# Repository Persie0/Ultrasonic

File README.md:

# Ultrasonic audio bench prototypes

Two independent design families, five editable KiCad projects. **These are electrical prototypes, not finished or exposure-certified speakers.** Start with a dummy capacitor and the arm link open.

| Design | Hardware | Build and test |
|---|---|---|
| [ESP32 original](designs/esp32-digital/) | External ESP32 DevKit, 5 V driver | [Build](designs/esp32-digital/BUILD.md) · [Test](designs/esp32-digital/TEST.md) |
| [ESP32 passive](designs/esp32-digital/minimum-cost/) | Four resistors; lowest additional parts cost | [Guide](designs/esp32-digital/minimum-cost/README.md) |
| [ESP32 integrated](designs/esp32-digital/integrated/) | USB power/programming, onboard ESP32, ten DNP positions | [Illustrated guide](designs/esp32-digital/integrated/BUILD_TEST.md) |
| [Analog DDS](designs/analog-dds/) | External DDS, Nano and analog line source | [Build](designs/analog-dds/BUILD.md) · [Test](designs/analog-dds/TEST.md) |
| [GreatScott reference PWM](designs/analog-dds/reference-pwm/) | Reference-derived logic controller, no power stage | [Guide](designs/analog-dds/reference-pwm/BUILD_TEST.md) |

The ten optional positions share one current-limited output, not ten independently powered channels. The passive load sweep predicts sharply reduced voltage as capacitance increases; a working ten-speaker system is not demonstrated.

## Verification

- [Original designs: CI 45840044890](https://github.com/Persie0/Playground/actions/runs/45840044890): three clean KiCad projects, ESP32 and three Arduino builds, 243 RC cases.
- [New designs: CI 45846640684](https://github.com/Persie0/Playground/actions/runs/45846640684): two clean KiCad projects, 6,480 comparison cases, 4,860 ten-load cases and 648 power sensitivity cases (106 power cases outside assumed limits).
- [Review and release gates](VALIDATION.md): 263 unique pin/net matches across five designs, all verified; physical/RF/USB/power and acoustic gates remain.

Original GreatScott Arduino sketch is committed unchanged; the supplied PDF and Gerber ZIP are verified but not yet uploaded. See [source inventory](designs/analog-dds/SOURCE_FILES.md). The owner confirms permission to reshare the attachments.

No fabrication release. No acoustic output guarantee. Do not fit an acoustic load until the separate qualified exposure and hardware review is complete.

For the integrated board, see the [power-only bring-up](designs/esp32-digital/integrated/POWER_TEST.md) and [USB power review](designs/esp32-digital/integrated/POWER_REVIEW.md) before any audio tests.

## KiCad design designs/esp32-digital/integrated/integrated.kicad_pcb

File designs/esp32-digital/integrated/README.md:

# Integrated USB-powered ESP32 bench board

One PCB, no external development board, DDS, audio receiver or programmer. Original ESP32-WROOM-32E-N4 module soldered directly to PCB, AP7361C-33E-13 SOT223 regulator, CH340C USB-UART with built-in clock, USB-B power/data connector, boot/reset switches, current-limited passive output and ten optional on-board 40 kHz load footprints (all DNP). Default assembly is the 2.7 nF electrical dummy load with arm solder bridge open. Ten positions share the same current-limited differential circuit; they are not independent amplifier channels. TP1 is an unpopulated probe location. USB only for power and firmware flashing; Bluetooth Classic A2DP after flashing. No change to existing firmware or drive limits. Actual audible output and acoustic safety not established; do not fit transmitter until qualified testing. No external power amplifier, oscillator, or adjustment needed.

Board 68 × 87 mm, two layers, 31 footprints, 123 pads, 312 segments, 38 vias. Source-derived pad geometries from KiCad ESP32-WROOM-32, SOT-223, SOIC-16, TE USB-B vertical, 0805/1206 and TL3342; local simplified footprints; verify package dimensions, connector variant, exposed-pad stencil, thermal copper, antenna clearance and solder mask against datasheets. The antenna overhangs top edge; keep metal/enclosure away. Native KiCad 9 ERC/DRC passed with zero violations in [run 45846640684](https://github.com/Persie0/Playground/actions/runs/45846640684); 118 unique schematic pin IDs matched PCB nets. RF/USB/thermal/mechanical review remains pending. No fabrication release.

## Power and programming

USB power is a regulated 5 V input. The ESP32 supply design needs burst-current capability; this board is not verified to meet USB enumeration current limits or regulator thermal limits. Do not assume an arbitrary computer port is suitable. A powered data host does not by itself establish USB compliance. AP7361C fixed SOT223 pin 1 input, pin 2 ground, pin 3 output, tab ground; do not substitute the reversed SOT223R pinout. CH340C is powered at 3.3 V (V3 tied to VCC), RX/TX crossed; R232 has an internal pull-down in the documented device. Verify the exact device lot/datasheet. The regulator is nominally rated 1 A, but this PCB is not thermally qualified at 500 mA or 1 A. Hold BOOT, pulse RESET, release BOOT, then flash using esptool/ESP-IDF with manual reset (no automatic DTR/RTS circuit). For programming use a suitable powered USB host; unplug after flashing, use USB supply and pair Bluetooth. Keep JP1 open. Fit C7 dummy only for electrical testing. Never connect external voltage or grounded test clip to either differential terminal.

## References

- https://documentation.espressif.com/esp32-wroom-32e_esp32-wroom-32ue_datasheet_en.html
- https://docs.espressif.com/projects/esp-hardware-design-guidelines/en/latest/esp32/schematic-checklist.html
- https://www.diodes.com/datasheet/download/AP7361C.pdf
- https://www.wch-ic.com/products/CH340.html
- https://www.murata.com/-/media/webrenewal/products/sensor/ultrasonic/open/datasheet_maopn.ashx

No full-power acoustic mode. The ten positions remain unpopulated by default. See [ten-load model](ten_load_simulation.md). See [build/test](BUILD_TEST.md) and [power model](power_simulation.md).

## Review status

See [overall release gates](../../../VALIDATION.md). A native DRC pass does not establish a verified RF ground plane, USB impedance/ESD compliance, regulator transient response or acoustic operation.

## Power-only diagnostic and revised USB review

Start with [POWER_TEST.md](POWER_TEST.md), not the audio firmware. [POWER_REVIEW.md](POWER_REVIEW.md) documents 756 additional screening cases, verified datasheet conditions and USB limitations. No PCB or output change in this review; no hardware release.

## Local ground-copper candidate

See [layout audit and candidate generation](POWER_COPPER.md). The existing validated PCB is retained; the proposed local ground zones are generated separately and require native fill and DRC. They are not a fabrication release or a measured thermal improvement.

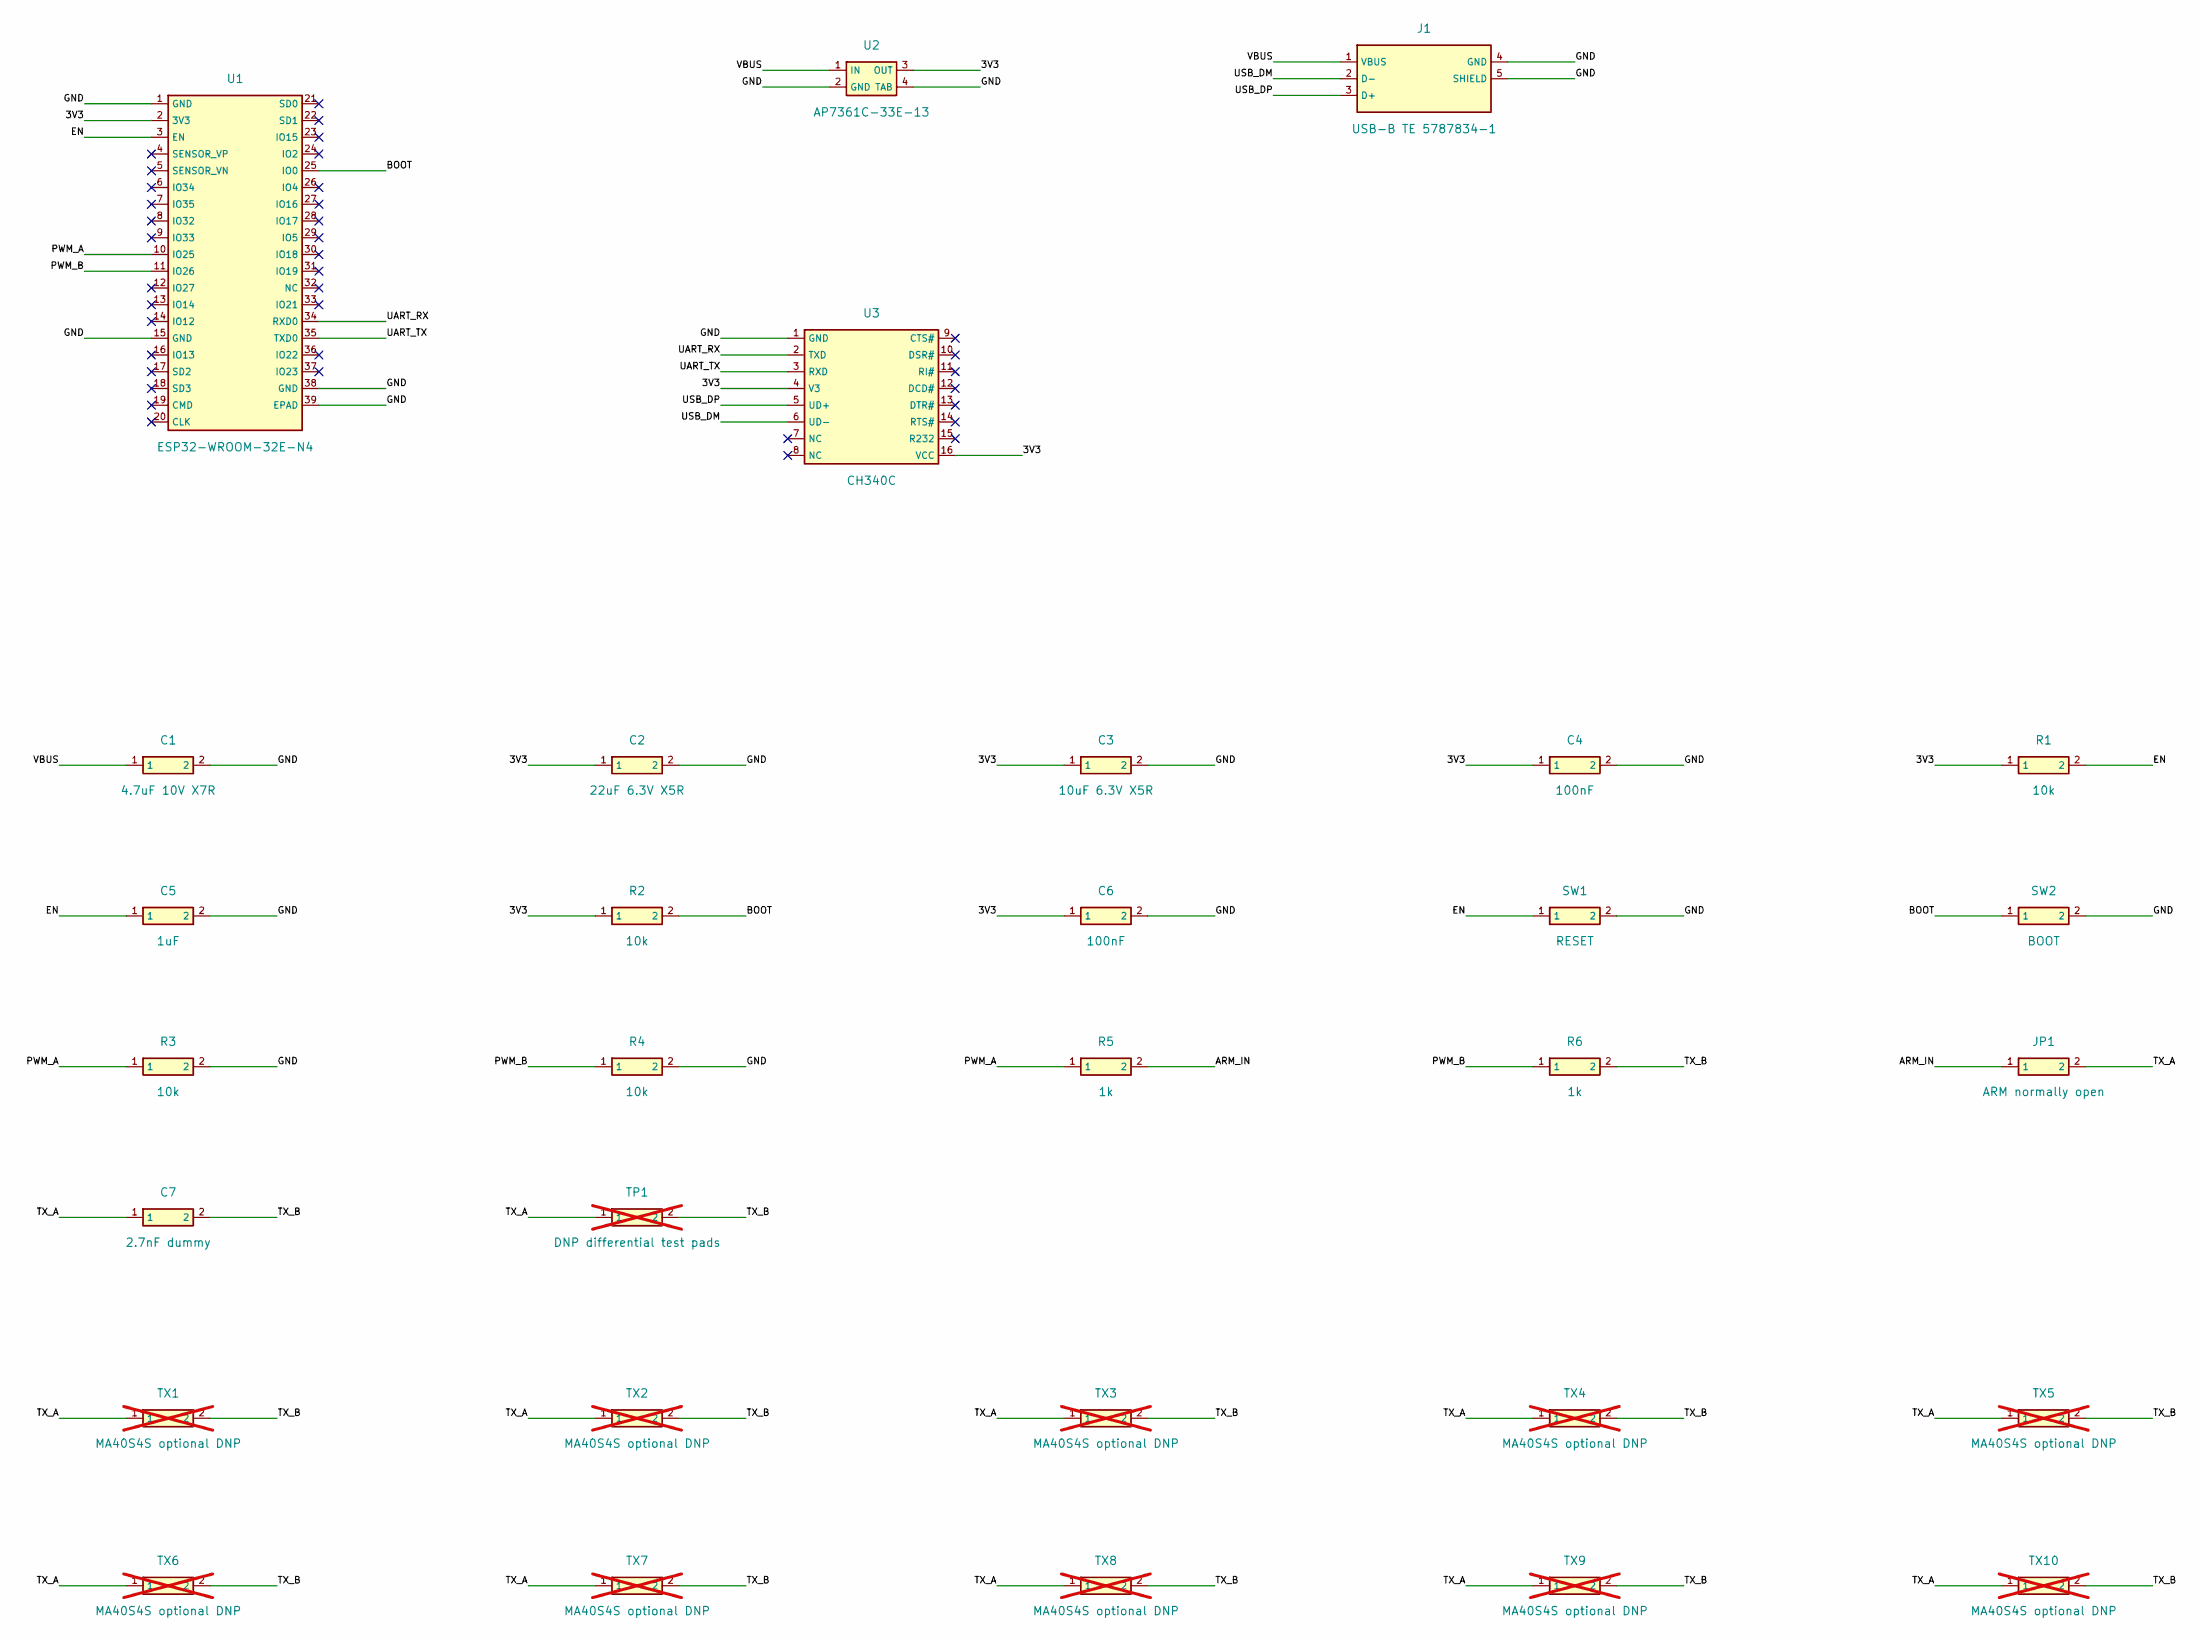
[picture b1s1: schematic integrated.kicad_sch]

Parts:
C1: 4.7uF 10V X7R; C1206
C2: 22uF 6.3V X5R; C1206
C3: 10uF 6.3V X5R; C1206
C4, C6: 100nF; C0805
C5: 1uF; C0805
C7: 2.7nF dummy; C0805
J1: USB-B TE 5787834-1; USB_B_VERTICAL
JP1: ARM normally open; SOLDERJUMPER
R1, R2, R3, R4: 10k; R0805
R5, R6: 1k; R0805
SW1: RESET; TACT_TL3342
SW2: BOOT; TACT_TL3342
TP1: DNP differential test pads; MA40S4S; not fitted
TX1, TX2, TX3, TX4, TX5, TX6, TX7, TX8, TX9, TX10: MA40S4S optional DNP; MA40S4S; not fitted
U1: ESP32-WROOM-32E-N4; ESP32_WROOM_32E
U2: AP7361C-33E-13; SOT223
U3: CH340C; SOIC16

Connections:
3V3: C2.1, C3.1, C4.1, C6.1, R1.1, R2.1, U1.2 (3V3), U2.3 (OUT), U3.4 (V3), U3.16 (VCC)
ARM_IN: JP1.1, R5.2
BOOT: R2.2, SW2.1, U1.25 (IO0)
EN: C5.1, R1.2, SW1.1, U1.3 (EN)
GND: C1.2, C2.2, C3.2, C4.2, C5.2, C6.2, J1.4 (GND), J1.5 (SHIELD), R3.2, R4.2, SW1.2, SW2.2, U1.1 (GND), U1.15 (GND), U1.38 (GND), U1.39 (EPAD), U2.2 (GND), U2.4 (TAB), U3.1 (GND)
PWM_A: R3.1, R5.1, U1.10 (IO25)
PWM_B: R4.1, R6.1, U1.11 (IO26)
TX_A: C7.1, JP1.2, TP1.1, TX1.1, TX2.1, TX3.1, TX4.1, TX5.1, TX6.1, TX7.1, TX8.1, TX9.1, TX10.1
TX_B: C7.2, R6.2, TP1.2, TX1.2, TX2.2, TX3.2, TX4.2, TX5.2, TX6.2, TX7.2, TX8.2, TX9.2, TX10.2
UART_RX: U1.34 (RXD0), U3.2 (TXD)
UART_TX: U1.35 (TXD0), U3.3 (RXD)
USB_DM: J1.2 (D-), U3.6 (UD-)
USB_DP: J1.3 (D+), U3.5 (UD+)
VBUS: C1.1, J1.1 (VBUS), U2.1 (IN)

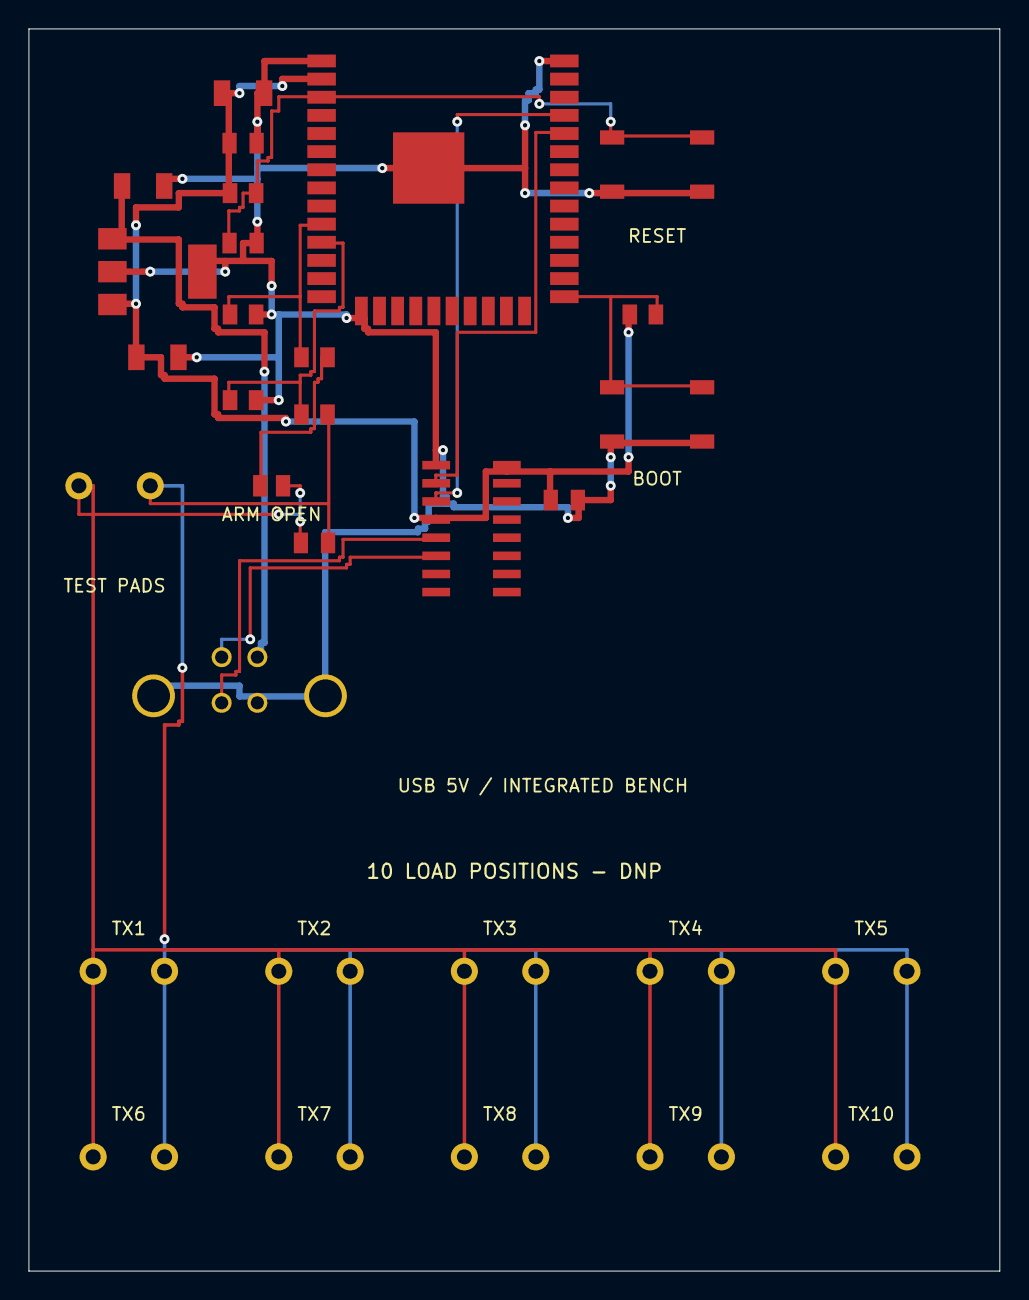
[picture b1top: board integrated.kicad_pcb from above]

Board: 2 copper layers, 68.0 x 87.0 mm, 31 parts (0 on the bottom side), 14 nets.

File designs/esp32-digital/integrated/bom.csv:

Reference,Quantity,Value,Footprint,Assembly
U1,1,ESP32-WROOM-32E-N4,ESP32_WROOM_32E,Fit
U2,1,AP7361C-33E-13,SOT223,Fit
U3,1,CH340C,SOIC16,Fit
J1,1,USB-B TE 5787834-1,USB_B_VERTICAL,Fit
C1,1,4.7uF 10V X7R,C1206,Fit
C2,1,22uF 6.3V X5R,C1206,Fit
C3,1,10uF 6.3V X5R,C1206,Fit
C4,1,100nF,C0805,Fit
R1,1,10k,R0805,Fit
C5,1,1uF,C0805,Fit
R2,1,10k,R0805,Fit
C6,1,100nF,C0805,Fit
SW1,1,RESET,TACT_TL3342,Fit
SW2,1,BOOT,TACT_TL3342,Fit
R3,1,10k,R0805,Fit
R4,1,10k,R0805,Fit
R5,1,1k,R0805,Fit
R6,1,1k,R0805,Fit
JP1,1,ARM normally open,SOLDERJUMPER,Fit
C7,1,2.7nF dummy,C0805,Fit
TP1,1,DNP differential test pads,MA40S4S,DNP
TX1,1,MA40S4S optional DNP,MA40S4S,DNP
TX2,1,MA40S4S optional DNP,MA40S4S,DNP
TX3,1,MA40S4S optional DNP,MA40S4S,DNP
TX4,1,MA40S4S optional DNP,MA40S4S,DNP
TX5,1,MA40S4S optional DNP,MA40S4S,DNP
TX6,1,MA40S4S optional DNP,MA40S4S,DNP
TX7,1,MA40S4S optional DNP,MA40S4S,DNP
TX8,1,MA40S4S optional DNP,MA40S4S,DNP
TX9,1,MA40S4S optional DNP,MA40S4S,DNP
TX10,1,MA40S4S optional DNP,MA40S4S,DNP

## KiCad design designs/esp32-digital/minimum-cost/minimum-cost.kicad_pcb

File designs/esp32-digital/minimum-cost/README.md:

# Minimum-cost passive-only ESP32 bench interface

Independent lower-output variant of the validated TC4427A board. Same firmware and original ESP32 DevKit; no extra IC or 5 V power input on this PCB. Four resistors, three inexpensive headers and one removable shunt. 31 x 24 mm, two layers, 15 pads, 18 tracks, no vias. Static clearance minimum 0.746 mm and all six nets connected; native KiCad ERC/DRC passed with zero violations in [run 45846640684](https://github.com/Persie0/Playground/actions/runs/45846640684). All 15 unique pin IDs matched PCB nets. Estimated passive BOM EUR 0.15–0.70 before shipping, PCB and ESP32; prices are planning assumptions rather than quotes. The cheapest electrical prototype uses existing breadboard/jumper wires instead of ordering a PCB. This board is not a performance-equivalent alternative to the TC4427A; lower voltage and higher series resistance substantially reduce output. It is intended for isolated capacitive dummy loads only until physical validation and an appropriate acoustic exposure review. Never connect an array, amplifier, external supply or grounded load to the output.

## Build and test

Inspect the KiCad project, verify ERC/DRC and physical component fit before ordering. Solder four resistors and headers; leave J2 open. J1 pin 1 common ground, pin 2 GPIO25, pin 3 GPIO26. No 5 V or 3.3 V supply pin. J3 is differential, neither pin is ground. Flash the unchanged [ESP32 firmware](../firmware/) with the board disconnected. Power only the DevKit normally; check the pins at idle and during streaming with an oscilloscope referenced only to DevKit ground. Power off, fit a nonpolar 2.2–2.7 nF dummy capacitor at J3, and close J2 only during supervised electrical tests. Verify boot/pause/disconnect muting, check each GPIO output and differential voltage with two grounded channels and math subtraction, record current and temperature, then power off and remove the jumper. No acoustic validation or manufacture approval. See [simulation](../simulation/minimum_cost.md).

Physical and acoustic validation remain pending. See [review](../../../VALIDATION.md).

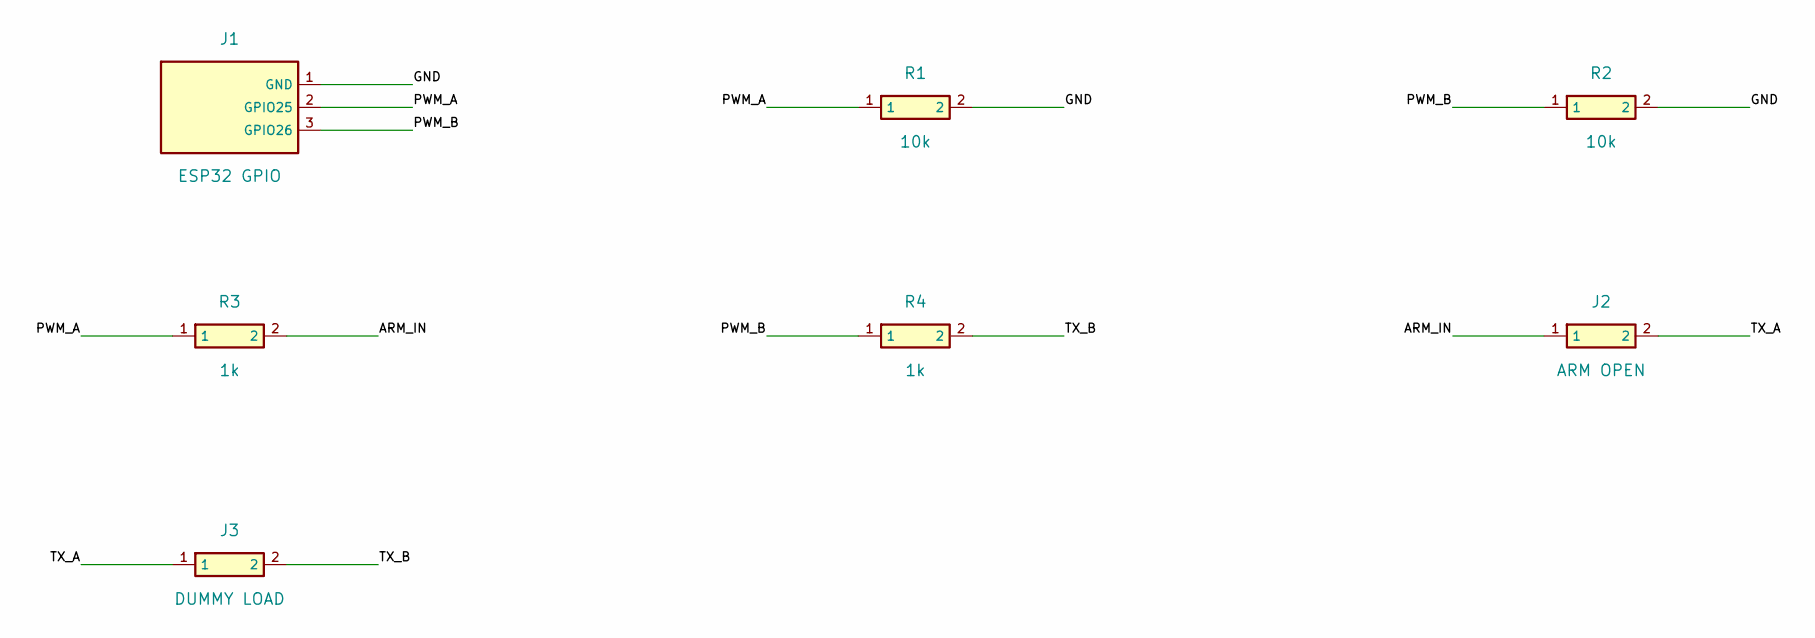
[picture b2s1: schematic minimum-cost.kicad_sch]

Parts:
J1: ESP32 GPIO; Header3
J2: ARM OPEN; Header2H
J3: DUMMY LOAD; Header2V
R1, R2: 10k; Axial
R3, R4: 1k; Axial

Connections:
ARM_IN: J2.1, R3.2
GND: J1.1 (GND), R1.2, R2.2
PWM_A: J1.2 (GPIO25), R1.1, R3.1
PWM_B: J1.3 (GPIO26), R2.1, R4.1
TX_A: J2.2, J3.1
TX_B: J3.2, R4.2

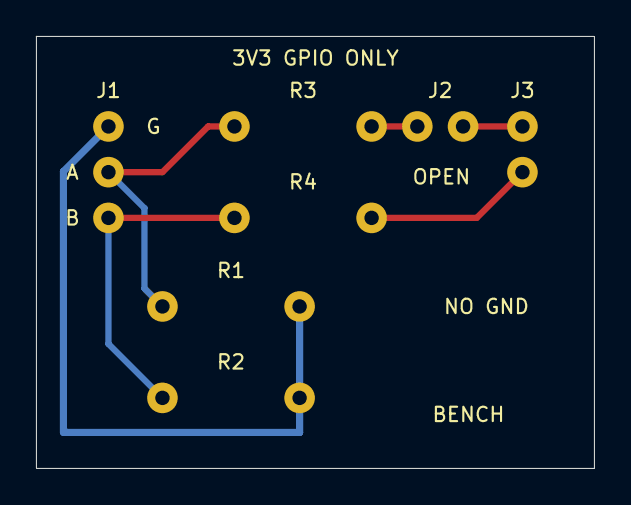
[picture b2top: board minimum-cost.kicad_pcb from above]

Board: 2 copper layers, 31.0 x 24.0 mm, 7 parts (0 on the bottom side), 6 nets.

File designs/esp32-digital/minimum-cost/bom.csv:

Reference,Quantity,Value,Notes
R1 R2,2,10k,axial 1/4W 7.62mm
R3 R4,2,1k,axial 1/4W 7.62mm
J1,1,1x3 2.54mm header,GPIO and common GND only
J2,1,1x2 2.54mm header and shunt,open by default
J3,1,1x2 2.54mm header,differential dummy load; neither pin ground
MOD1,1,ESP32-WROOM-32 DevKit,original Bluetooth Classic capable ESP32

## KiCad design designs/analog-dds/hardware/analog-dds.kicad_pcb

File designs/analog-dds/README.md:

# Analog DDS prototype (GreatScott-inspired)

Independent low-voltage analog comparator experiment, based on the general architecture discussed in [GreatScott's directional speaker video](https://www.youtube.com/watch?v=B8ss4KqcuXU) and [project post](https://www.patreon.com/GreatScott/posts/directional-119558088). The original schematic PDF, Arduino sketch and transmitter Gerbers were subsequently supplied and inspected. See [source inventory](SOURCE_FILES.md). The fixed-bias board below remains an independent alternative, not the creator's circuit. A separate [reference-derived PWM controller PCB](reference-pwm/) preserves the original analog topology and adjustments.

The supplied schematic uses Arduino Nano, AD9833, MCP602, LM393 and potentiometers, and ends at PWMOUT. The H-bridge power stage is not included in the supplied schematic. This independent version instead uses an external Nano + AD9833 module, external Bluetooth line-out module, fixed passive bias/attenuation, LM393 comparator and TC4427A single-ended 5 V output. The second comparator and driver channels are unused and defined. No trimmers, no high-voltage power stage, no array. An output coupling capacitor blocks steady DC; J4 is a normally-open arm jumper. The fixed bias is only appropriate for a verified raw low-voltage triangle output; not all DDS modules expose the same waveform. Audio compatibility and audible output are not demonstrated.

- [KiCad PCB and schematic](hardware/)
- [Build tutorial](BUILD.md)
- [Test tutorial](TEST.md)
- [BOM](hardware/bom.csv)
- [Nano DDS sketch](firmware/dds_setup/dds_setup.ino)

Experimental single-transmitter/dummy-load design only. Native ERC and DRC passed with zero violations (see [validation](VALIDATION.md)); physical and acoustic validation are outstanding; do not fabricate or use until the release gates are reviewed.

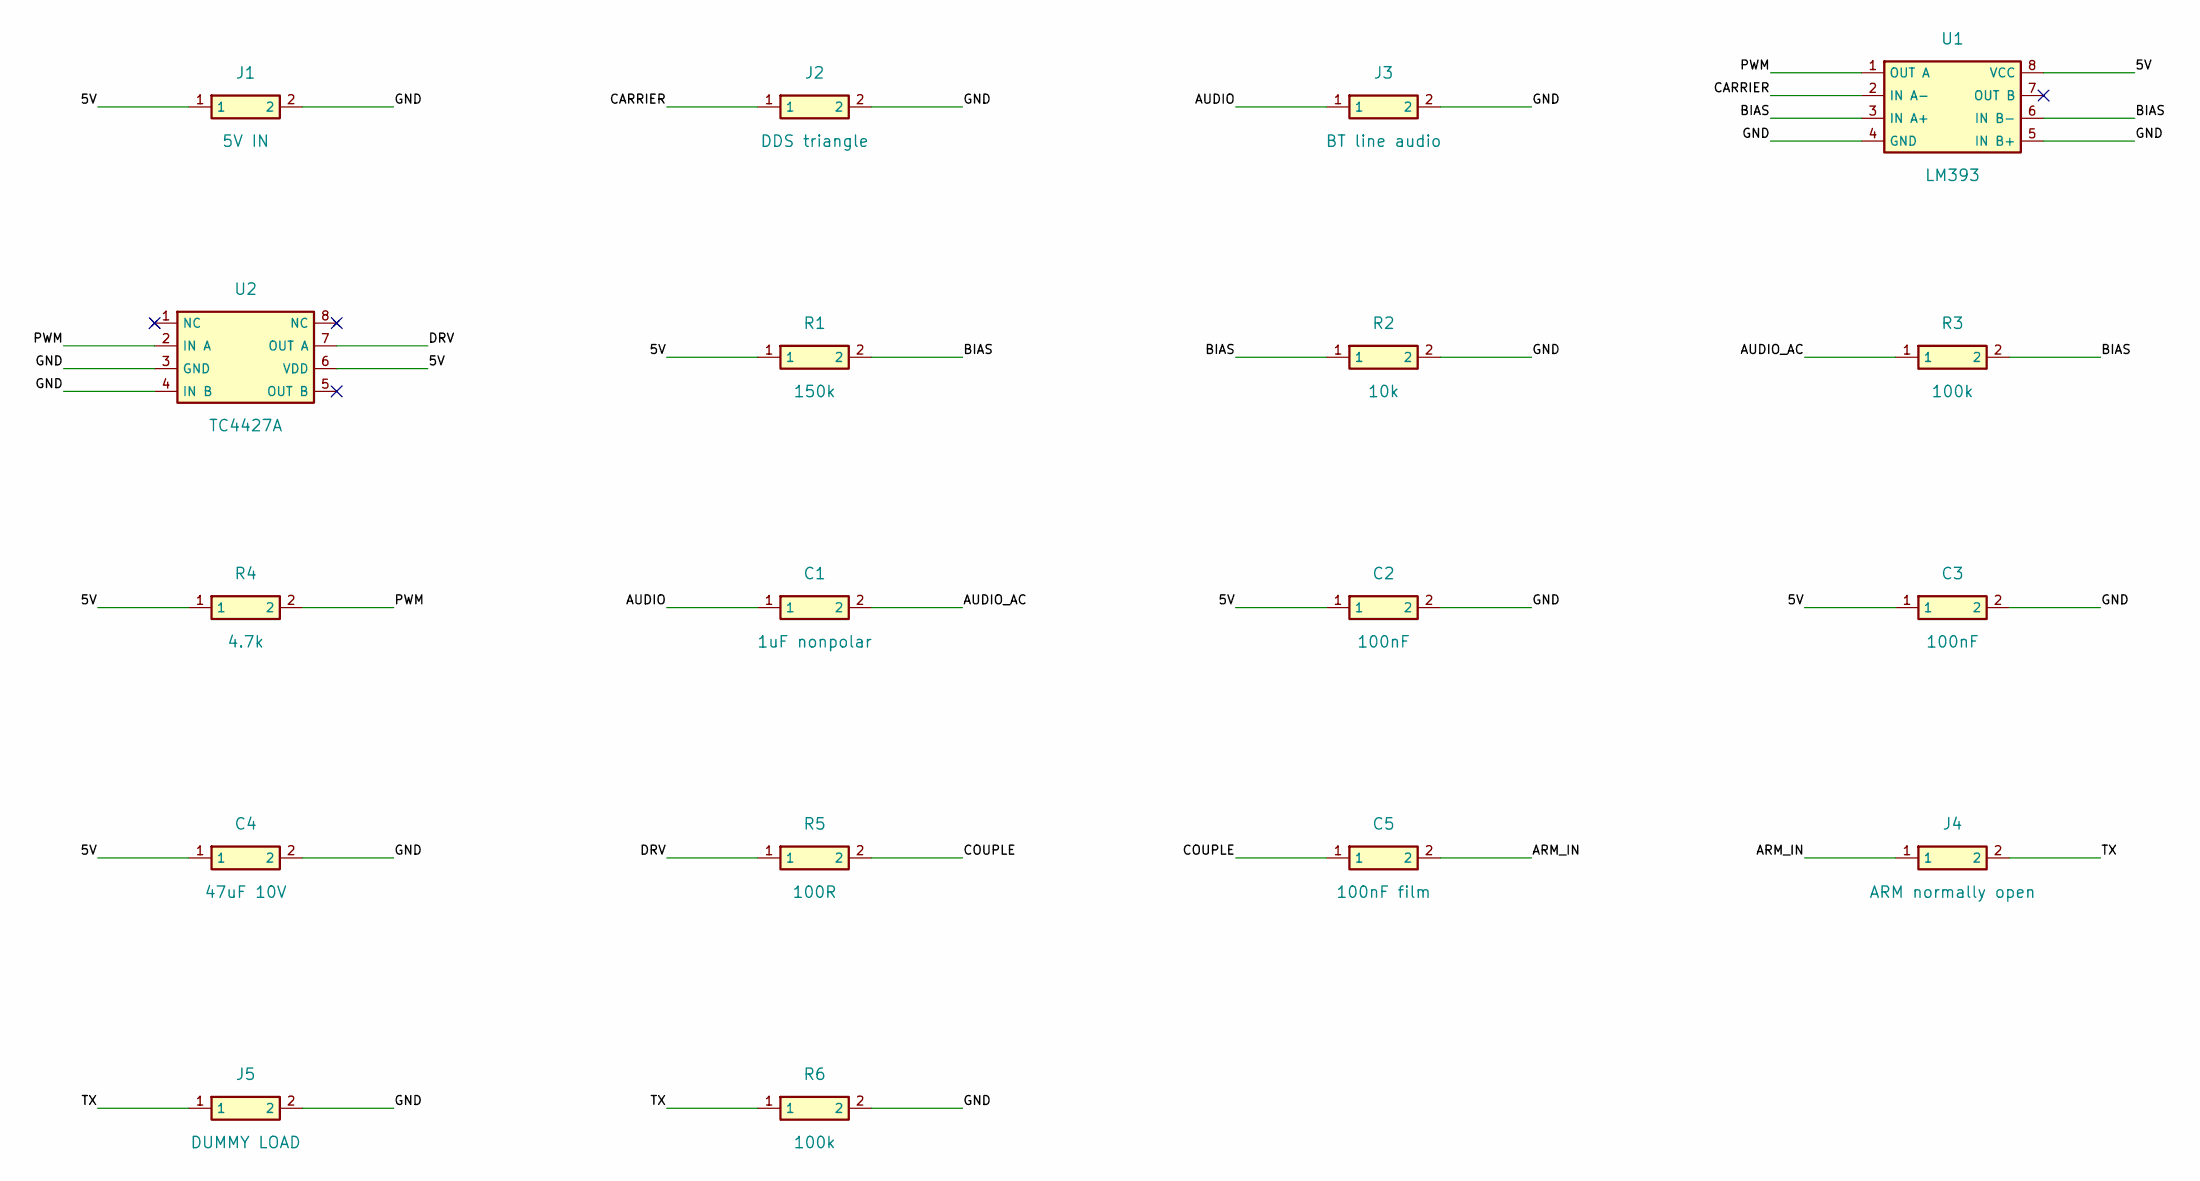
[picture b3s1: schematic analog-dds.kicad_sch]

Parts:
C1: 1uF nonpolar; Film508
C2, C3: 100nF; Disc254
C4: 47uF 10V; Radial254
C5: 100nF film; Film508
J1: 5V IN; Header2
J2: DDS triangle; Header2
J3: BT line audio; Header2
J4: ARM normally open; Header2H
J5: DUMMY LOAD; Header2
R1: 150k; Axial
R2: 10k; Axial
R3, R6: 100k; Axial
R4: 4.7k; Axial
R5: 100R; Axial
U1: LM393; DIP8
U2: TC4427A; DIP8

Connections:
5V: C2.1, C3.1, C4.1, J1.1, R1.1, R4.1, U1.8 (VCC), U2.6 (VDD)
ARM_IN: C5.2, J4.1
AUDIO: C1.1, J3.1
AUDIO_AC: C1.2, R3.1
BIAS: R1.2, R2.1, R3.2, U1.3 (IN A+), U1.6 (IN B-)
CARRIER: J2.1, U1.2 (IN A-)
COUPLE: C5.1, R5.2
DRV: R5.1, U2.7 (OUT A)
GND: C2.2, C3.2, C4.2, J1.2, J2.2, J3.2, J5.2, R2.2, R6.2, U1.4 (GND), U1.5 (IN B+), U2.3 (GND), U2.4 (IN B)
PWM: R4.2, U1.1 (OUT A), U2.2 (IN A)
TX: J4.2, J5.1, R6.1

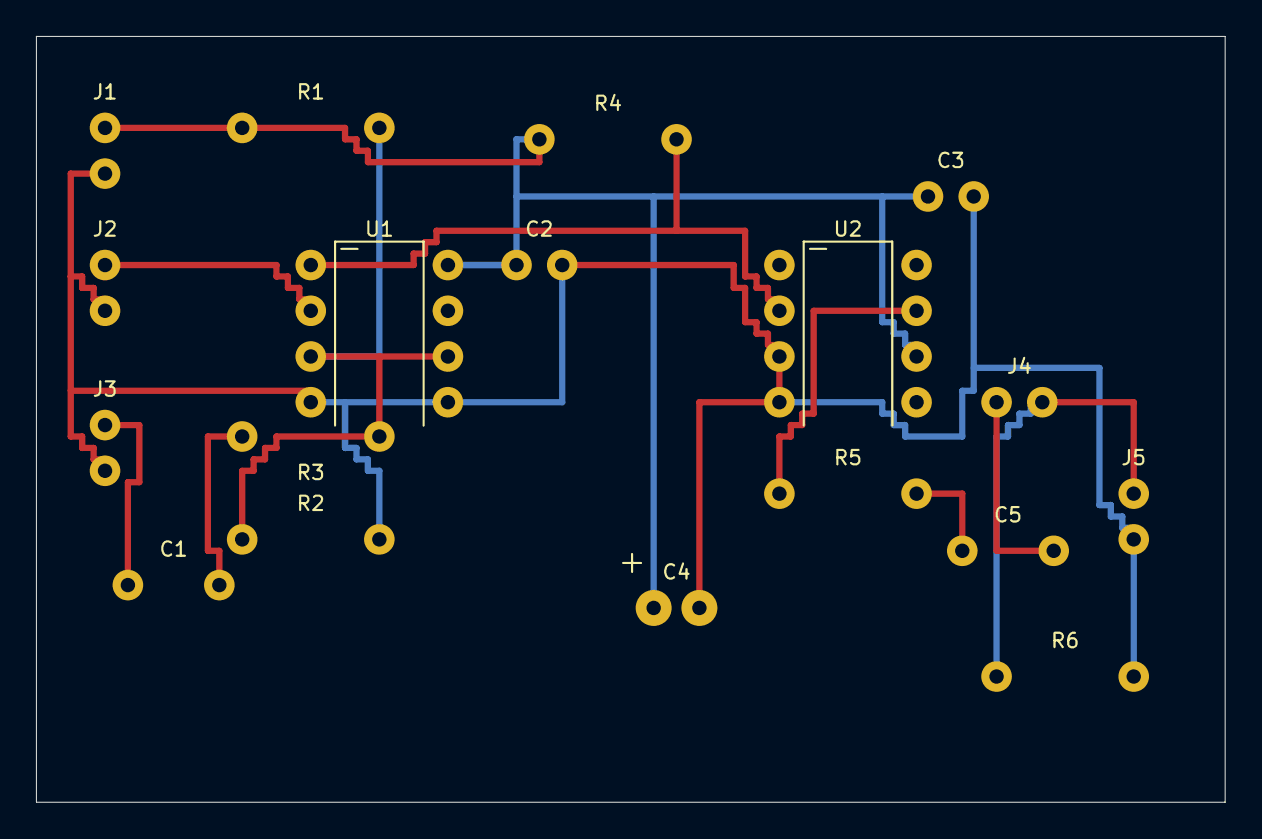
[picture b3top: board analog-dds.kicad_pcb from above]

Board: 2 copper layers, 66.0 x 42.5 mm, 18 parts (0 on the bottom side), 11 nets.

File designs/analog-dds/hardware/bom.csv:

Reference,Quantity,Value,Notes
J1,1,5V IN,2.54 mm header
J2,1,DDS triangle,2.54 mm header
J3,1,BT line audio,2.54 mm header
U1,1,LM393,DIP-8
U2,1,TC4427A,DIP-8
R1,1,150k,1/4W axial 7.62 mm
R2,1,10k,1/4W axial 7.62 mm
R3,1,100k,1/4W axial 7.62 mm
R4,1,4.7k,1/4W axial 7.62 mm
C1,1,1uF nonpolar,nonpolar 5.08 mm lead pitch
C2,1,100nF,ceramic 2.54 mm lead pitch
C3,1,100nF,ceramic 2.54 mm lead pitch
C4,1,47uF 10V,radial 2.54 mm lead pitch
R5,1,100R,1/4W axial 7.62 mm
C5,1,100nF film,nonpolar 5.08 mm lead pitch
J4,1,ARM normally open,2.54 mm header
J5,1,DUMMY LOAD,2.54 mm header
R6,1,100k,1/4W axial 7.62 mm
MOD1,1,Arduino Nano,ATmega328P
MOD2,1,AD9833 breakout,verified 25 MHz and logic compatibility
MOD3,1,Bluetooth A2DP receiver,ground-referenced line out

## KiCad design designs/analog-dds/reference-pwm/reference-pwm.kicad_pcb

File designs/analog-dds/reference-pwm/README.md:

# GreatScott reference PWM logic board

New editable PCB and schematic based on the user-supplied one-page GreatScott PDF, dated 2024-12-29 (file dated 2024-12-30). Credit: GreatScott, [original post](https://www.patreon.com/GreatScott/posts/directional-119558088). This PCB layout is independently generated, not the supplied transmitter PCB. It ends at logic-level PWMOUT; **no power amplifier, H-bridge or transmitter connection** is included. The original PDF also ends at PWMOUT.

Preserves the reference's two adjustable 50k potentiometers, MCP602 amplifier, 100k/20k feedback network, 1uF audio coupling, LM393 comparator and 1k pull-up. Differences: external Nano and DDS module headers, additional supply bypass/bulk capacitors, defined unused analog channels, nonpolar input coupling capacitor, ground-referenced logic test header. Verify component footprints (especially potentiometers) before fabrication. Do not connect a transducer to PWMOUT. The adjustment-free sibling design remains in ../hardware; neither implementation is acoustically validated.

Board: 68.58 × 40.64 mm, 16 footprints, 54 plated pads, 222 segments, 0 vias. Grid routing completed; KiCad native ERC/DRC passed with zero violations; mechanical fit and physical verification remain outstanding. See [validation](../VALIDATION.md). Open [project](reference-pwm.kicad_pro). See [source inventory](../SOURCE_FILES.md) and [build/test guide](BUILD_TEST.md).

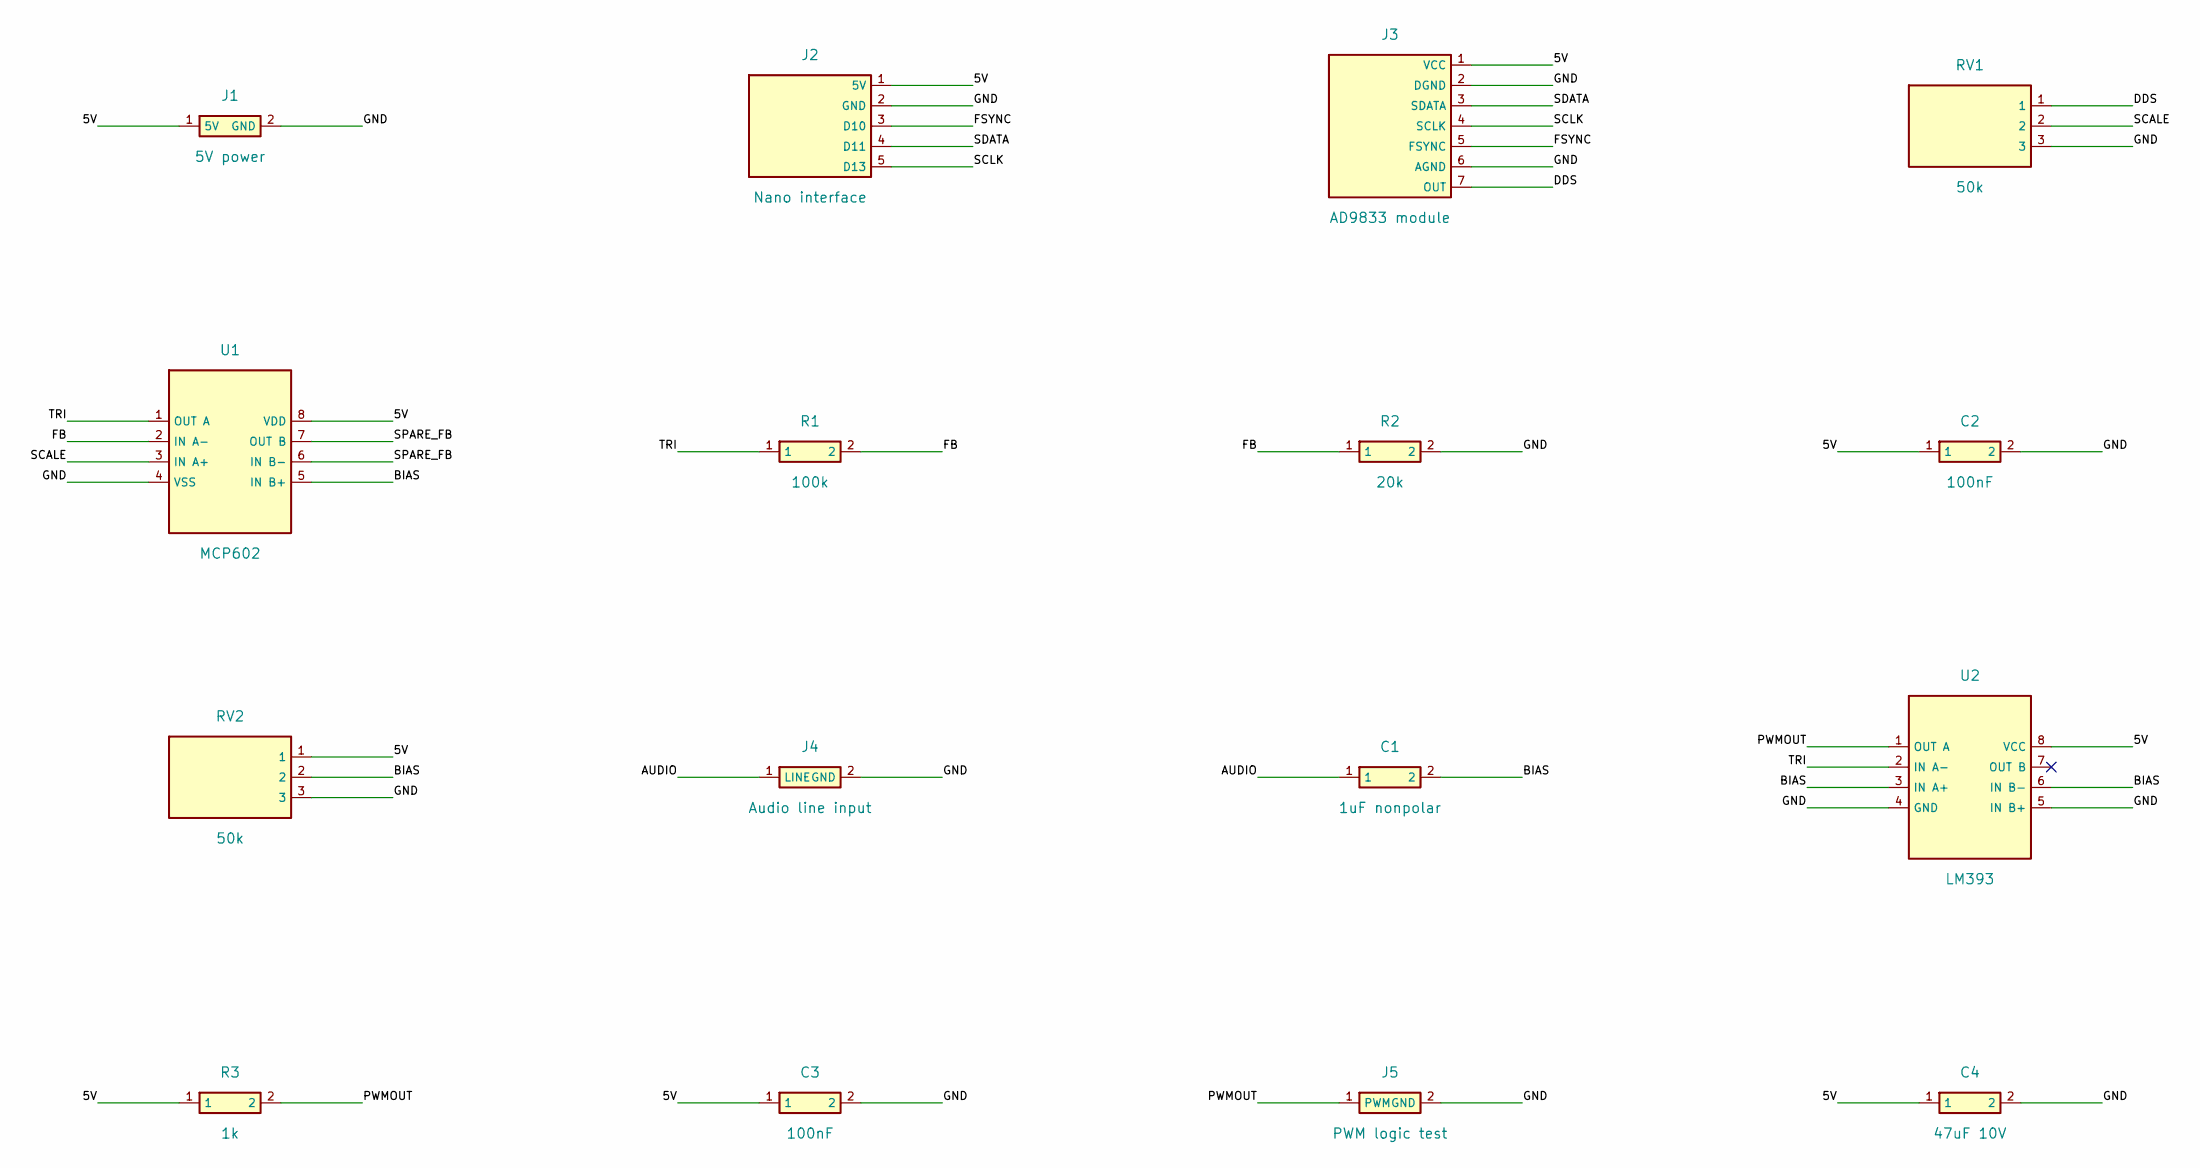
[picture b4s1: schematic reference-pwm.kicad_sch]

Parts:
C1: 1uF nonpolar; Film
C2, C3: 100nF; Disc
C4: 47uF 10V; Radial
J1: 5V power; Header2
J2: Nano interface; Header5
J3: AD9833 module; Header7
J4: Audio line input; Header2
J5: PWM logic test; Header2
R1: 100k; Axial
R2: 20k; Axial
R3: 1k; Axial
RV1, RV2: 50k; Pot3
U1: MCP602; DIP8
U2: LM393; DIP8

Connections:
5V: C2.1, C3.1, C4.1, J1.1 (5V), J2.1 (5V), J3.1 (VCC), R3.1, RV2.1, U1.8 (VDD), U2.8 (VCC)
AUDIO: C1.1, J4.1 (LINE)
BIAS: C1.2, RV2.2, U1.5 (IN B+), U2.3 (IN A+), U2.6 (IN B-)
DDS: J3.7 (OUT), RV1.1
FB: R1.2, R2.1, U1.2 (IN A-)
FSYNC: J2.3 (D10), J3.5 (FSYNC)
GND: C2.2, C3.2, C4.2, J1.2 (GND), J2.2 (GND), J3.2 (DGND), J3.6 (AGND), J4.2 (GND), J5.2 (GND), R2.2, RV1.3, RV2.3, U1.4 (VSS), U2.4 (GND), U2.5 (IN B+)
PWMOUT: J5.1 (PWM), R3.2, U2.1 (OUT A)
SCALE: RV1.2, U1.3 (IN A+)
SCLK: J2.5 (D13), J3.4 (SCLK)
SDATA: J2.4 (D11), J3.3 (SDATA)
SPARE_FB: U1.6 (IN B-), U1.7 (OUT B)
TRI: R1.1, U1.1 (OUT A), U2.2 (IN A-)

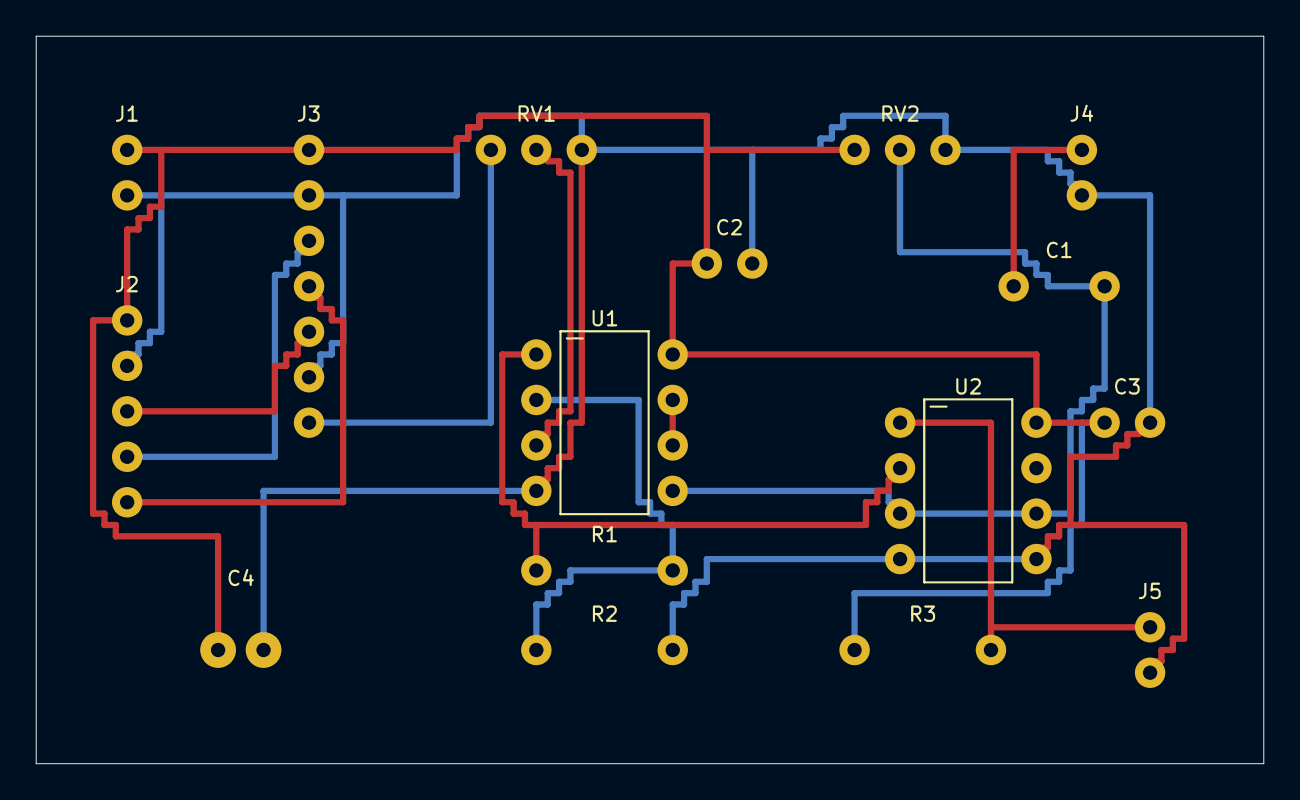
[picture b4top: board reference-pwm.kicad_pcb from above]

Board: 2 copper layers, 68.6 x 40.6 mm, 16 parts (0 on the bottom side), 13 nets.

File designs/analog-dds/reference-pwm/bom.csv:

Reference,Quantity,Value,Notes
J1,1,5V power,2.54 mm header
J2,1,Nano interface,2.54 mm header
J3,1,AD9833 module,2.54 mm header
RV1,1,50k,3-pin inline 2.54 mm; verify actual footprint or use wires
U1,1,MCP602,DIP-8
R1,1,100k,1/4W axial 7.62 mm
R2,1,20k,1/4W axial 7.62 mm
C2,1,100nF,2.54 mm ceramic
RV2,1,50k,3-pin inline 2.54 mm; verify actual footprint or use wires
J4,1,Audio line input,2.54 mm header
C1,1,1uF nonpolar,nonpolar 5.08 mm
U2,1,LM393,DIP-8
R3,1,1k,1/4W axial 7.62 mm
C3,1,100nF,2.54 mm ceramic
J5,1,PWM logic test,2.54 mm header
C4,1,47uF 10V,radial 2.54 mm
MOD1,1,Arduino Nano,external
MOD2,1,AD9833 module,external

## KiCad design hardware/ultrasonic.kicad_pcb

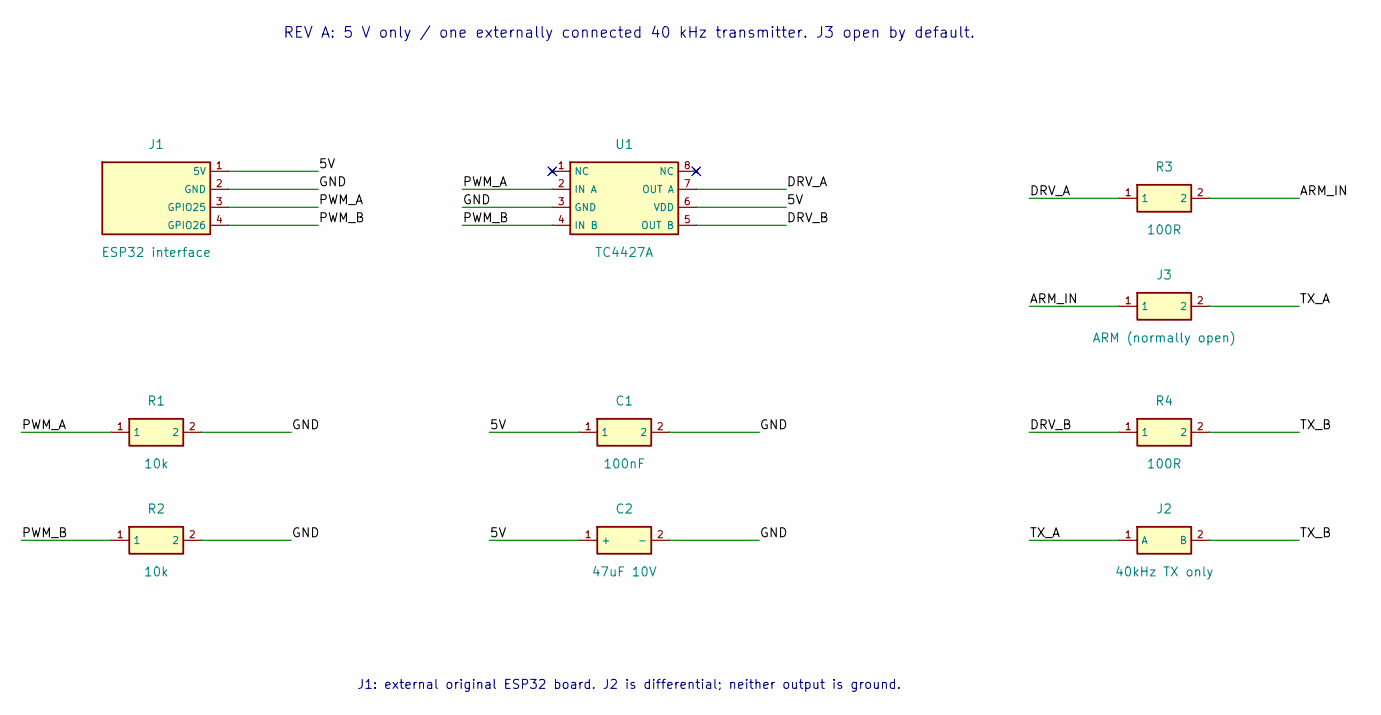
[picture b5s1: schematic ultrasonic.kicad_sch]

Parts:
C1: 100nF; C_Disc_D5.0mm_W2.5mm_P2.50mm
C2: 47uF 10V; CP_Radial_D6.3mm_P2.50mm
J1: ESP32 interface; PinHeader_1x04_P2.54mm_Vertical
J2: 40kHz TX only; TerminalBlock_Phoenix_MKDS-1,5-2-5.08_1x02_P5.08mm_Horizont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
J3: ARM (normally open); PinHeader_1x02_P2.54mm_Horizontal
R1, R2: 10k; R_Axial_DIN0207_L6.3mm_D2.5mm_P7.62mm_Horizontal
R3, R4: 100R; R_Axial_DIN0207_L6.3mm_D2.5mm_P7.62mm_Horizontal
U1: TC4427A; DIP-8_W7.62mm

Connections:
5V: C1.1, C2.1 (+), J1.1 (5V), U1.6 (VDD)
ARM_IN: J3.1, R3.2
DRV_A: R3.1, U1.7 (OUT A)
DRV_B: R4.1, U1.5 (OUT B)
GND: C1.2, C2.2 (-), J1.2 (GND), R1.2, R2.2, U1.3 (GND)
PWM_A: J1.3 (GPIO25), R1.1, U1.2 (IN A)
PWM_B: J1.4 (GPIO26), R2.1, U1.4 (IN B)
TX_A: J2.1 (A), J3.2
TX_B: J2.2 (B), R4.2

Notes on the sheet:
REV A: 5 V only / one externally connected 40 kHz transmitter. J3 open by default.
J1: external original ESP32 board. J2 is differential; neither output is ground.
